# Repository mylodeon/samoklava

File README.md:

# samoklava
## An autogenerated split 36 key keyboard

## Disclaimer

This is an early experimental prototype. Please do not rely on the autogenerated files and double check them manually
before sending them off to a PCB fab. The author and other random strangers on the internet have been able to produce
working keyboard prototypes from this repo; this does not mean that everything will work every time.

The author(s) waive(s) responsibility for any damage or regulatory violations caused by using this software (see
license). Please consult your local regulations around radio frequencies and what's allowed for DIY projects in your
country.

left | right
-|-	
 | 

A 5x3 split keyboard with 3 thumb keys. There is nothing unique about the keyboard layout. It's inspired by Corne and
Kyria, and has the exact number of keys needed for the [Miryoku](https://github.com/manna-harbour/miryoku) layout.

The interesting thing about this keyboard is that it's a declarative design:
* Layout is declared using [Ergogen](https://github.com/mrzealot/ergogen/). New: no fork needed!
* The build system uses Ergogen to translate YAML to a KiCad PCB and plate files for FR-4 fab or laser cutting
* uses [kicad-automation-scripts](https://github.com/productize/kicad-automation-scripts) and [FreeRouting](https://github.com/freerouting/freerouting) to **automatically route the traces on the PCB**
* uses [KiKit](https://github.com/yaqwsx/KiKit) to render PCB previews (see top of this file) and production-ready **Gerber files**

## Features

* A slider switch for battery for wireless Promicro clones (tested with nice!nano); the slider can be
  shorted with a jumper if `CONFIG_ZMK_SLEEP` is preferred.
* Wired operation with QMK should be possible but is not tested; TRRS footprints are included and routed. The pinout is
  identical with a five-column Corne sans the RGBLEDs.
* Reset switches are easily accessible. The footprints used are the same as on the Corne.

## How to

If you would like to modify this:
* fork it
* change `config.yaml` to your liking
* push your changes; the `build.yml` GitHub Workflow will pick it up, autoroute and generate Gerbers, all in a zip file.
  See https://github.com/soundmonster/samoklava/actions
* or:
  * make sure to have Docker CLI and NodeJS installed
  * run `make setup clean all`
  * check the `output` folder for KiCad PCBs and Gerbers

See the [workflow](.github/workflows/build.yml) or the [Makefile](Makefile) for more details.
See [my ZMK config](https://github.com/soundmonster/samoklava-zmk-config) for a suggested keymap.

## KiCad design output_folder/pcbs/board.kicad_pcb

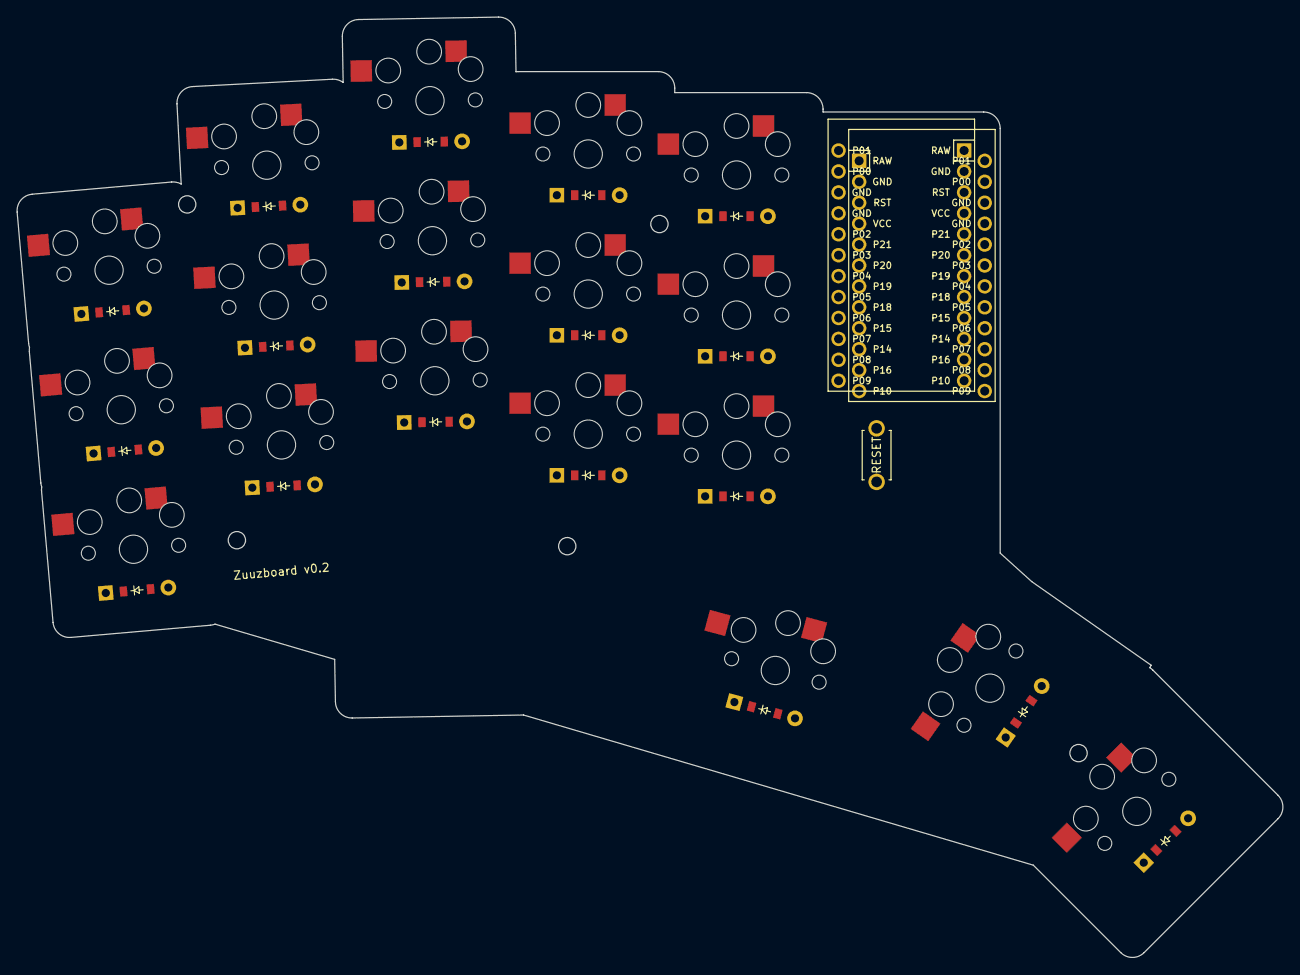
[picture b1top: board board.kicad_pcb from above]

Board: 2 copper layers, 153.6 x 114.1 mm, 39 parts (0 on the bottom side), 40 nets, no tracks yet.

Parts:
B1: ResetSW
D1, D2, D3, D4, D5, D6, D7, D8, D9, D10, D11, D12, D13, D14, D15, D16, D17, D18: ComboDiode
MCU1, MCU2: ProMicro
S1, S2, S3, S4, S5, S6, S7, S8, S9, S10, S11, S12, S13, S14, S15, S16, S17, S18: PG1350

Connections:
GND: B1.2, MCU1.2, MCU1.15, MCU1.16, MCU2.2, MCU2.15, MCU2.16
P0: MCU1.14, MCU2.14
P1: MCU1.13, MCU2.13
P2: MCU1.17, MCU2.17
P3: MCU1.18, MCU2.18
P7: MCU1.22, MCU2.22
P8: MCU1.23, MCU2.23
P9: MCU1.24, MCU2.24
P10: MCU1.12, MCU2.12
P21: MCU1.5, MCU2.5
RAW: MCU1.1, MCU2.1
RST: B1.1, MCU1.3, MCU2.3
VCC: MCU1.4, MCU2.4
col_index: MCU1.20, S10.2, S11.2, S12.2, S17.2
col_inner: MCU1.19, S13.2, S14.2, S15.2, S18.2
col_middle: MCU1.21, S7.2, S8.2, S9.2, S16.2
col_pinky: MCU1.6, S1.2, S2.2, S3.2
col_ring: MCU1.7, S4.2, S5.2, S6.2
far_thumb: D18.2, S18.1
home_thumb: D17.2, S17.1
index_bottom: D10.2, S10.1
index_home: D11.2, S11.1
index_top: D12.2, S12.1
inner_bottom: D13.2, S13.1
inner_home: D14.2, S14.1
inner_top: D15.2, S15.1
middle_bottom: D7.2, S7.1
middle_home: D8.2, S8.1
middle_top: D9.2, S9.1
near_thumb: D16.2, S16.1
pinky_bottom: D1.2, S1.1
pinky_home: D2.2, S2.1
pinky_top: D3.2, S3.1
ring_bottom: D4.2, S4.1
ring_home: D5.2, S5.1
ring_top: D6.2, S6.1
row_bottom: D1.1, D4.1, D7.1, D10.1, D13.1, MCU1.11
row_home: D2.1, D5.1, D8.1, D11.1, D14.1, MCU1.9
row_thumb: D16.1, D17.1, D18.1, MCU1.8
row_top: D3.1, D6.1, D9.1, D12.1, D15.1, MCU1.10

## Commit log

2024-03-28 Rotate and stagger
2024-03-28 Zuuzboard
2024-03-28 promicro
2024-03-28 Use nice nano
2024-03-28 Change net
2024-03-28 Remove another diode
2024-03-28 Fix column net
2024-03-28 Fix typo
2024-03-28 Remove choc hotswap footprint
2024-03-28 Update to rae-dux
2024-03-28 More
2024-03-28 Literal overwrite
2024-03-28 Remove diode
2024-03-28 Rownet
2024-03-28 Column net
2024-04-05 Add splay
2024-04-05 More splay
2024-04-07 Add files
2024-04-07 Switch to Heawood Graph
2024-04-07 Swith to new ergogen standard
2024-04-07 More updates
2024-04-07 Update rotary
2024-04-07 Update size
2024-04-07 Update board size
2024-04-07 Fix nets
2024-04-07 Fix top plate
2024-04-14 Add diodes
2024-04-14 Reduce board for autorouting
2024-04-14 PUT BACK DIODES
2024-04-14 Remove more components
2024-04-14 Fix P17
2024-04-14 Simpler footprint
2024-04-14 No MCU
2024-04-14 Try autoroute
2024-04-14 Add noref_via
2024-04-14 Move back to Haewood matrix
2024-04-15 v.03
2024-04-15 v.0.3 Fix routing
2024-04-15 v.0.3 Fix routing thumbs
2024-04-15 v.0.3
2024-04-28 Add debouncer
2024-04-28 Add rotary encoder
2024-04-28 Rev Board
2024-04-28 Change board
2024-04-28 Combochock
2024-04-29 Zuuz v0.004 board
2024-04-29 Zuuz v0.4 combochoc
